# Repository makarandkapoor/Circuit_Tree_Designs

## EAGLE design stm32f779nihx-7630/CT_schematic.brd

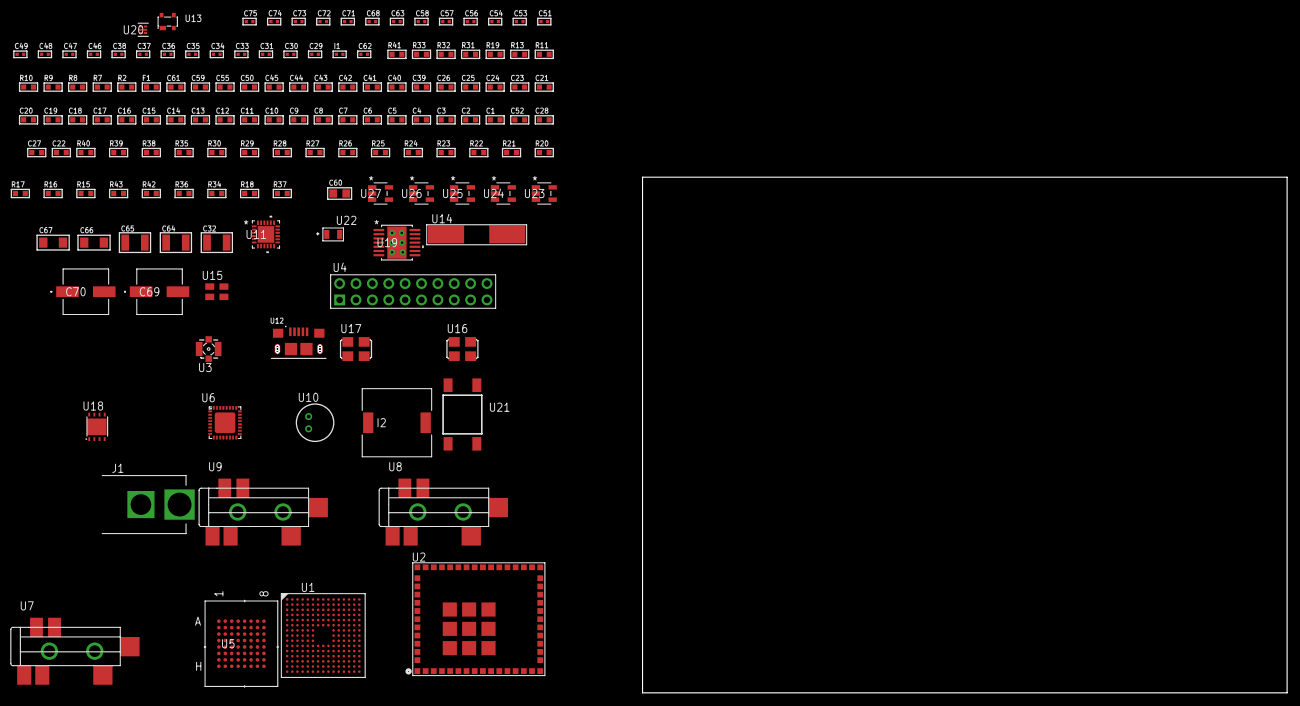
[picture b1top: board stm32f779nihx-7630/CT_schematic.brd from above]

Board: 2 copper layers, 142 parts (0 on the bottom side), 121 nets, no tracks yet.

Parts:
C1, C25, C39, C40, C41, C42, C43, C44, C45, C50, C55, C61: 1e-06; C0603
C2, C3, C4, C5, C6, C7, C8, C9, C10, C11, C12, C13, C14, C15, C16, C17, C18, C19, C20, C21, C23, C26: 1e-07; C0603
C22: 4.7e-06; C0603
C24: 1e-08; C0603
C27, C28, C52: 2.2e-06; C0603
C29, C30: 1e-11; C0402
C31: 1e-12; C0402
C32, C64, C65: 2.2e-05; C1210
C33, C34, C35, C36, C46, C47, C48, C49, C63, C68: 1e-07; C0402
C37, C38, C51, C53, C54, C56, C57, C58, C71, C72, C73, C74, C75: 1e-08; C0402
C59: 8e-07; R0603
C60: 1e-05; C0805
C62: 3.3e-09; C0402
C66, C67: 1e-05; C1206
C69, C70: 0.0001; EXV-9H
F1: 240.0; L0603
I1: 3.6e-09; C0402
I2: 5.2e-06; DR1040
J1: PJ-037B; PJ-037B_PACKAGE
R2: 1000.0; R0603
R7, R8, R9, R10: 4700.0; R0603
R11, R13: 2200.0; R0603
R15, R16, R17, R20, R21, R22, R23, R24, R25, R26, R27, R28, R29, R30, R39, R40: 10000.0; R0603
R18, R34, R36: 100000.0; R0603
R19: 2700.0; R0603
R31, R32: 1270.0; R0603
R33: 8060.0; R0603
R35: 36000.0; R0603
R37: 71007.101651032; R0603
R38: 22000.0; R0603
R41: 9100.0; R0603
R42: 680000.0; R0603
R43: 120000.0; R0603
U1: STM32F779NIH6; TFBGA216
U2: CC3200MODR1M2AMOBT; LGA63S127P16X13_2050X1750X150
U3: 73412-0114; COAXIAL_C
U4: TST-110-05-T-D-RA
U5: MT28EW128ABA1HPC-0SIT; LBGA-64
U6: SGTL5000XNAA3; QFN-32
U7, U8, U9: SJ-43515TS-SMT-TR
U10: WM-64PCT; WM-64PC
U11: USB3317C-CP-TR; QFN-24
U12: 10118193-0001LF; FCI_10118193-0001LF
U13: prtr5v0u2ax; SOT143B
U14: ABLS-25.000MHZ-B2F-T
U15: ASEK-32.768KHz-ECST; ASEK
U16: ASFL-24.57MHZ-NCS; ASFL1
U17: ASFL1-26MHZ-NCS; ASFL1
U18: LP2951ACSDX/NOPB; WSON-8
U19: tps54325PWP; HTSSOP14
U20: TPS3895ADRYR; SON-6
U21: 4-1437565-2; SW_4-1437565-2
U22: Q65110A2395; LGM67K-G1J2-24-Z
U23, U24, U25, U26, U27: nc7sz125m5x; NC7SZ125M5X

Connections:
CLK_CRYSTAL_U1_G1: C29.1, U1.G1, U14.1
CLK_CRYSTAL_U1_H1: C30.1, U1.H1, U14.2
CLK_U1_E1: U1.E1, U15.3
CLK_U6_21: U6.21, U16.3
CLK_U11_23: U11.23, U17.3
GND: C1.2, C2.2, C3.2, C4.2, C5.2, C6.2, C7.2, C8.2, C9.2, C10.2, C11.2, C12.2, C13.2, C14.2, C15.2, C16.2, C17.2, C18.2, C19.2, C20.2, C21.2, C22.2, C23.2, C24.2, C25.2, C26.2, C27.2, C28.2, C29.2, C30.2, C31.2, C32.2, C33.2, C34.2, C35.2, C36.2, C37.2, C38.2, C46.2, C47.2, C48.2, C49.2, C50.2, C51.2, C52.2, C53.2, C54.2, C55.2, C56.2, C57.2, C58.2, C59.2, C60.2, C61.2, C62.2, C64.2, C65.2, C66.2, C67.2, C68.2, C69.2, C70.2, C71.2, C72.2, C73.2, C74.2, C75.2, J1.2, R2.2, R15.2, R17.2, R18.2, R19.2, R25.2, R32.2, R33.2, R36.2, R38.2, R41.2, R43.2, U1.F2, U1.F6, U1.F7, U1.F8, U1.F9, U1.F10, U1.G6, U1.G10, U1.G12, U1.H6, U1.H10, U1.J6, U1.J10, U1.K6, U1.K7, U1.K8, U1.K9, U1.K10, U1.L6, U1.M1, U1.N1, U2.1, U2.2, U2.16, U2.27, U2.28, U2.30, U2.32, U2.38, U2.43, U2.55, U2.56, U2.57, U2.58, U2.59, U2.60, U2.61, U2.62, U2.63, U3.1, U3.2, U3.3, U3.4, U4.4, U4.6, U4.8, U4.10, U4.12, U4.14, U4.16, U4.18, U4.20, U5.E8, U5.H2, U5.H7, U6.1, U6.3, U6.7, U6.EXP, U8.1, U9.1, U10.2, U11.25, U12.5, U12.6, U12.7, U12.8, U12.9, U13.1, U15.2, U16.2, U17.2, U18.3, U18.4, U18.PAD, U19.5, U19.8, U19.9, U19.15, U20.2, U22.C, U23.2, U23.3, U24.1, U24.3, U25.1, U25.3, U26.1, U26.3, U27.1, U27.3
NET_U1_A7: R11.1, U1.A7, U2.3
NET_U1_B4: R13.1, U1.B4, U2.4
NET_U1_E5: R16.1, U1.E5
NET_U1_E6: R15.1, U1.E6
NET_U1_E11: C28.1, U1.E11
NET_U1_J1: R9.1, U1.J1, U26.4
NET_U1_L5: R17.1, U1.L5
NET_U1_L11: C27.1, U1.L11
NET_U1_R1: C24.1, C25.1, F1.1, U1.P1, U1.R1
NET_U1_R15: U21.3, U21.4
NET_U2_21: R18.1, U2.21
NET_U2_23: R19.1, U2.23
NET_U2_35: R8.1, U2.35, U25.4
NET_U3_1: C31.1, I1.1, U3.1
NET_U4_19: R25.1, U4.19
NET_U5_B4: R29.1, U5.B4
NET_U5_B5: R7.1, U5.B5, U24.4
NET_U6_10: C49.1, U6.10
NET_U6_29: R31.1, U6.29
NET_U6_31: R32.1, U6.31
NET_U7_1: U6.4, U7.1
NET_U7_2: U6.2, U7.2
NET_U7_5: U6.6, U7.5
NET_U8_2: C40.1, U8.2
NET_U8_5: C39.1, U8.5
NET_U9_2: C42.1, C43.1, U9.2
NET_U9_5: C41.1, U9.5
NET_U9_13: C42.2, C43.2
NET_U10_1: C44.1, C45.1, C50.1, U6.16, U10.1
NET_U10_15: C44.2, C45.2
NET_U11_4: C52.1, U11.4
NET_U11_22: R10.1, U11.22, U27.4
NET_U11_24: R33.1, U11.24
NET_U12_1: C55.1, U11.2, U12.1, U13.4
NET_U12_2: U11.5, U12.2, U13.3
NET_U12_3: U11.6, U12.3, U13.2
NET_U18_5: R34.1, U18.5
NET_U18_7: R35.2, R36.1, U18.7
NET_U19_2: R37.2, R38.1, U19.2
NET_U19_3: C61.1, U19.3
NET_U19_4: C62.1, U19.4
NET_U19_10: C63.1, I2.1, U19.10, U19.11
NET_U19_12: C63.2, U19.12
NET_U20_1: R40.1, R41.1, U20.1
NET_U20_3: R42.2, R43.1, U20.3
NET_U20_4: R39.1, U20.4, U23.4, U24.2, U25.2, U26.2, U27.2
NET_U21_1: R2.1, U21.1, U21.2
PROC_FMC_A0: U1.D2, U5.E2
PROC_FMC_A1: U1.E2, U5.D2
PROC_FMC_A2: U1.G2, U5.C2
PROC_FMC_A3: U1.H2, U5.A2
PROC_FMC_A4: U1.J2, U5.B2
PROC_FMC_A5: U1.K3, U5.D3
PROC_FMC_A6: U1.M6, U5.C3
PROC_FMC_A7: U1.N6, U5.A3
PROC_FMC_A8: U1.P6, U5.B6
PROC_FMC_A9: U1.M8, U5.A6
PROC_FMC_A10: U1.N7, U5.C6
PROC_FMC_A11: U1.M7, U5.D6
PROC_FMC_A12: U1.M13, U5.B7
PROC_FMC_A13: U1.M12, U5.A7
PROC_FMC_A14: U1.N12, U5.C7
PROC_FMC_A15: U1.N11, U5.D7
PROC_FMC_A16: U1.N10, U5.E7
PROC_FMC_A17: U1.M10, U5.B3
PROC_FMC_A18: U1.M11, U5.C4
PROC_FMC_A19: U1.A2, U5.D5
PROC_FMC_A20: U1.A1, U5.D4
PROC_FMC_A21: U1.B1, U5.C5
PROC_FMC_A22: U1.B2, U5.B8
PROC_FMC_D0: U1.L12, U5.E3
PROC_FMC_D1: U1.K13, U5.H3
PROC_FMC_D2: U1.B12, U5.E4
PROC_FMC_D3: U1.C12, U5.H4
PROC_FMC_D4: U1.R8, U5.H5
PROC_FMC_D5: U1.N9, U5.E5
PROC_FMC_D6: U1.P9, U5.H6
PROC_FMC_D7: U1.R9, U5.E6
PROC_FMC_D8: U1.P10, U5.F3
PROC_FMC_D9: U1.R10, U5.G3
PROC_FMC_D10: U1.R12, U5.F4
PROC_FMC_D11: U1.P11, U5.G4
PROC_FMC_D12: U1.R11, U5.F5
PROC_FMC_D13: U1.L15, U5.G6
PROC_FMC_D14: U1.L14, U5.F6
PROC_FMC_D15: U1.K15, U5.G7
PROC_FMC_NBL0: R30.1, U1.A6, U5.F7
PROC_FMC_NE2: R26.1, U1.D9, U5.F2
PROC_FMC_NOE: R27.1, U1.D11, U5.G2
PROC_FMC_NWAIT: U1.B11, U5.A4
PROC_FMC_NWE: R28.1, U1.C10, U5.A5
PROC_I2S1_CK: U1.B8, U6.24
PROC_I2S1_SD: U1.A11, U6.26
PROC_I2S1_WS: U1.C8, U6.23
PROC_SYS_JTCK_SWCLK: R23.1, U1.A14, U4.9
PROC_SYS_JTDI: R21.1, U1.A13, U4.5
PROC_SYS_JTDO_SWO: U1.A10, U4.13
PROC_SYS_JTMS_SWDIO: R22.1, U1.A15, U4.7
PROC_SYS_JTRST: R20.1, U1.A9, U4.3
PROC_USB_OTG_HS_ULPI_CK: U1.P4, U11.12
PROC_USB_OTG_HS_ULPI_D0: U1.R2, U11.16
PROC_USB_OTG_HS_ULPI_D1: U1.R5, U11.15
PROC_USB_OTG_HS_ULPI_D2: U1.R4, U11.14
PROC_USB_OTG_HS_ULPI_D3: U1.P12, U11.13
PROC_USB_OTG_HS_ULPI_D4: U1.R13, U11.11
PROC_USB_OTG_HS_ULPI_D5: U1.L13, U11.10
PROC_USB_OTG_HS_ULPI_D6: U1.K14, U11.9
PROC_USB_OTG_HS_ULPI_D7: U1.A8, U11.8
PROC_USB_OTG_HS_ULPI_DIR: U1.F3, U11.19
PROC_USB_OTG_HS_ULPI_NXT: U1.H4, U11.18
PROC_USB_OTG_HS_ULPI_STP: U1.M2, U11.20
RST_OUT_U4_SRESET_B: R24.1, U4.15, U23.1
VCC_S1_12V5: C59.1, C66.1, C67.1, C69.1, C70.1, J1.1, U18.8, U19.7, U19.13, U19.14
VCC_TIER1_1V8: C46.1, C47.1, C54.1, C60.1, C71.1, C72.1, C73.1, C74.1, C75.1, R34.2, R35.1, U6.5, U6.30, U11.21, U18.1, U23.5, U24.5, U25.5, U26.5, U27.5
VCC_TIER1_3V3: C1.1, C2.1, C3.1, C4.1, C5.1, C6.1, C7.1, C8.1, C9.1, C10.1, C11.1, C12.1, C13.1, C14.1, C15.1, C16.1, C17.1, C18.1, C19.1, C20.1, C21.1, C22.1, C23.1, C26.1, C32.1, C33.1, C34.1, C35.1, C36.1, C37.1, C38.1, C48.1, C51.1, C53.1, C56.1, C57.1, C58.1, C64.1, C65.1, C68.1, F1.2, I2.2, R7.2, R8.2, R9.2, R10.2, R11.2, R13.2, R16.2, R20.2, R21.2, R22.2, R23.2, R24.2, R26.2, R27.2, R28.2, R29.2, R30.2, R31.2, R37.1, R39.2, R40.2, R42.1, U1.C1, U1.E7, U1.E8, U1.E9, U1.E10, U1.F4, U1.F5, U1.F11, U1.G5, U1.G11, U1.H5, U1.H11, U1.J5, U1.J11, U1.K5, U1.K11, U1.L7, U1.L8, U1.L9, U1.L10, U2.36, U2.37, U2.40, U4.1, U4.2, U5.D8, U5.F1, U5.G5, U6.20, U11.3, U11.17, U15.4, U16.4, U17.4, U19.1, U20.6

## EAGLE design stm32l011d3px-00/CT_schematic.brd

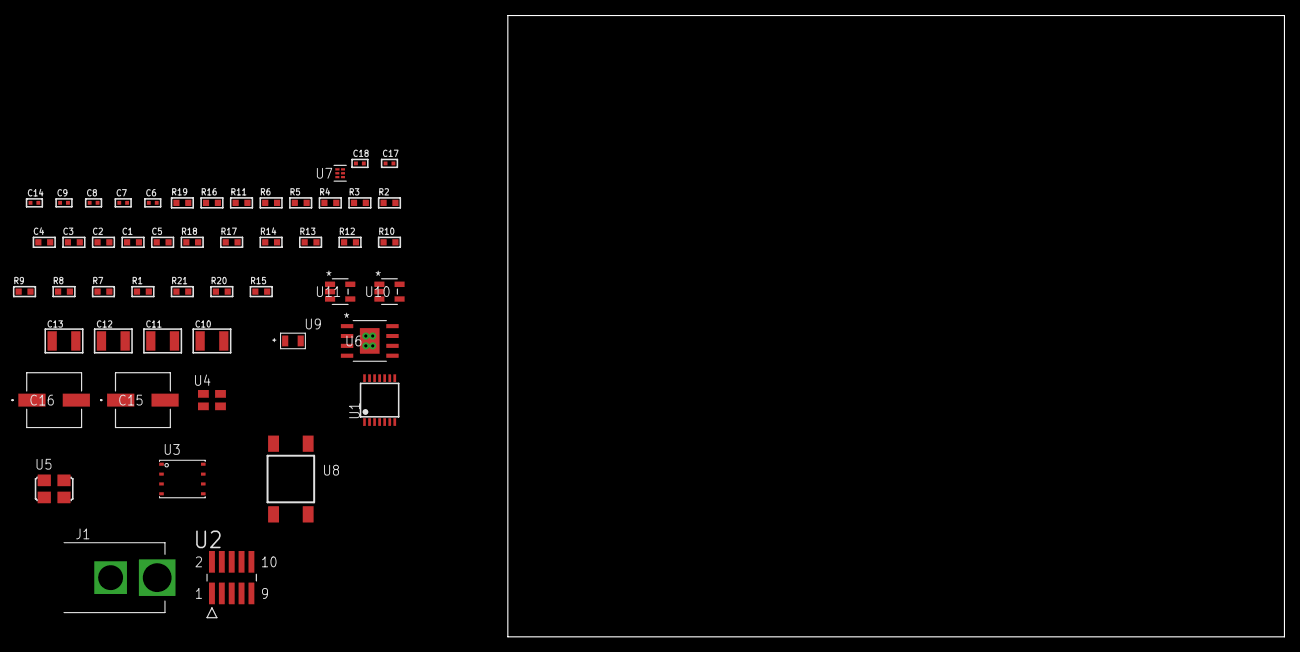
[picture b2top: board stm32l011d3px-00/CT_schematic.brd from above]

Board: 2 copper layers, 100.0 x 80.0 mm, 51 parts (0 on the bottom side), 23 nets, no tracks yet.

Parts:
C1, C2, C3, C4: 1e-07; C0603
C5: 4.7e-06; C0603
C6, C14: 1e-07; C0402
C7, C8, C9, C17, C18: 1e-08; C0402
C10, C11, C12, C13: 1e-05; C1210
C15, C16: 0.0001; EXV-9H
J1: PJ-037B; PJ-037B_PACKAGE
R1, R7, R8, R9, R10, R12, R13, R14, R17, R18: 10000.0; R0603
R2: 1000.0; R0603
R3: 1600.5; R0603
R4: 4700.0; R0603
R5, R6, R16: 2200.0; R0603
R11: 5.0; R0603
R15: 4031.5447154472; R0603
R19: 9100.0; R0603
R20: 680000.0; R0603
R21: 120000.0; R0603
U1: STM32L011D3P6; TSSOP14
U2: FTSH-105-01-L-DV-K; SAMTEC_FTSH-105-01-L-DV-K
U3: 24AA256-I/MF; DFN8-S
U4: ASEK-32.768KHz-ECST; ASEK
U5: ASFL1-12MHZ-NCS; ASFL1
U6: MIC5234YME; SOIC-8_EP
U7: TPS3895ADRYR; SON-6
U8: 4-1437565-2; SW_4-1437565-2
U9: Q65110A2395; LGM67K-G1J2-24-Z
U10, U11: nc7sz125m5x; NC7SZ125M5X

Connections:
CLK_U1_2: U1.2, U4.3
CLK_U1_5: U1.5, U5.3
GND: C1.2, C2.2, C3.2, C4.2, C5.2, C6.2, C7.2, C8.2, C9.2, C10.2, C11.2, C12.2, C13.2, C14.2, C15.2, C16.2, C17.2, C18.2, J1.2, R2.2, R7.2, R11.2, R16.2, R19.2, R21.2, U1.9, U2.3, U2.5, U3.4, U3.7, U4.2, U5.2, U6.7, U6.EPAD, U7.2, U9.C, U10.2, U10.3, U11.1, U11.3
NET_U1_1: R7.1, U1.1
NET_U1_4: R4.1, U1.4, U11.4
NET_U1_7: R5.1, U1.7, U3.6
NET_U1_8: R3.1, U1.8, U9.A
NET_U1_11: R1.1, U1.11, U8.3, U8.4
NET_U1_12: R6.1, U1.12, U3.5
NET_U2_9: R11.1, U2.9
NET_U3_1: R12.1, U3.1
NET_U3_2: R13.1, U3.2
NET_U3_3: R14.1, U3.3
NET_U6_4: R15.2, R16.1, U6.4
NET_U7_1: R18.1, R19.1, U7.1
NET_U7_3: R20.2, R21.1, U7.3
NET_U7_4: R17.1, U7.4, U10.4, U11.2
NET_U8_1: R2.1, U8.1, U8.2
PROC_SYS_SWCLK: R9.1, U1.14, U2.4
PROC_SYS_SWDIO: R10.1, U1.13, U2.2
RST_OUT_U2_JTAG_RST_B: R8.1, U2.10, U10.1
VCC_S1_16V8: C10.1, C11.1, C15.1, C16.1, J1.1, U6.5, U6.8
VCC_TIER1_3V3: C1.1, C2.1, C3.1, C4.1, C5.1, C6.1, C7.1, C8.1, C9.1, C12.1, C13.1, C14.1, C17.1, C18.1, R1.2, R3.2, R4.2, R5.2, R6.2, R8.2, R9.2, R10.2, R12.2, R13.2, R14.2, R15.1, R17.2, R18.2, R20.1, U1.10, U2.1, U3.8, U4.4, U5.4, U6.1, U7.6, U10.5, U11.5

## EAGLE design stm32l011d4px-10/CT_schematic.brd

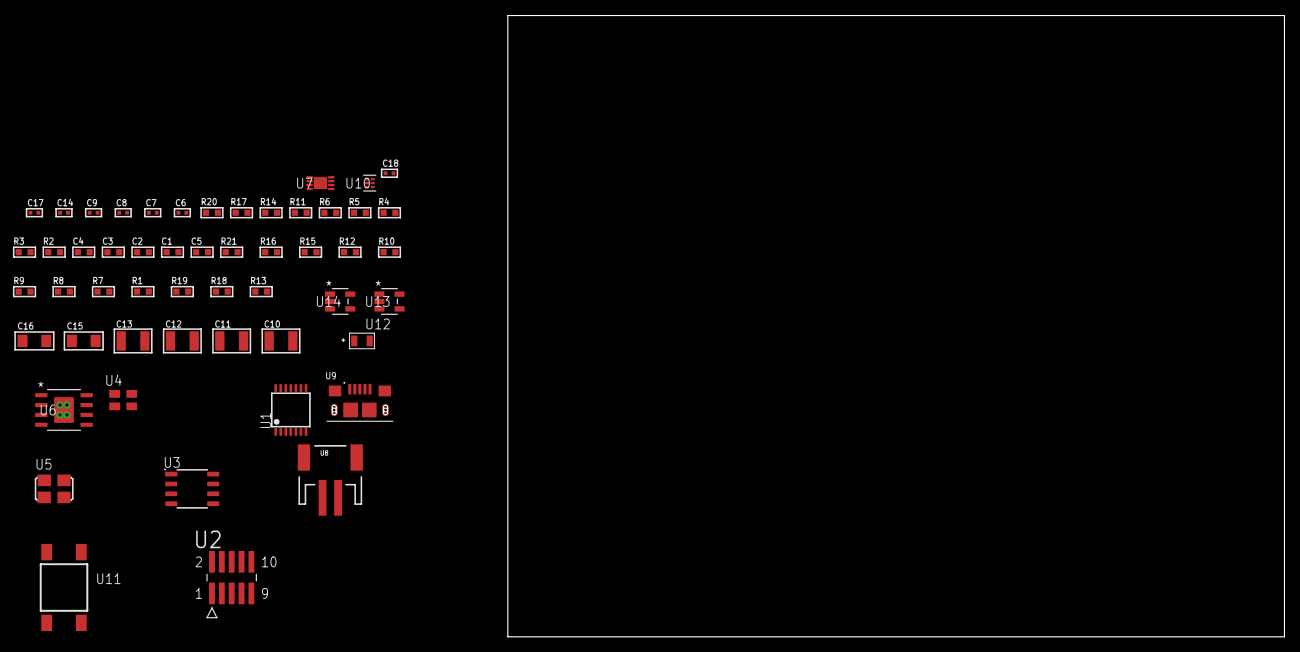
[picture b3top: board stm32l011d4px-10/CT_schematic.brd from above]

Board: 2 copper layers, 122.6 x 80.0 mm, 53 parts (0 on the bottom side), 24 nets, no tracks yet.

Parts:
C1, C2, C3, C4: 1e-07; C0603
C5: 4.7e-06; C0603
C6, C14: 1e-07; C0402
C7, C8, C9, C17, C18: 1e-08; C0402
C10, C11, C12, C13: 1e-05; C1210
C15, C16: 1e-05; C1206
R1, R7, R8, R9, R10, R12, R15, R16, R21: 10000.0; R0603
R2: 1000.0; R0603
R3: 1600.5; R0603
R4: 4700.0; R0603
R5, R6, R14: 2200.0; R0603
R11: 5.0; R0603
R13: 4031.5447154472; R0603
R17: 9100.0; R0603
R18: 680000.0; R0603
R19: 120000.0; R0603
R20: 2000.0; R0603
U1: STM32L011D4P7; TSSOP14
U2: FTSH-105-01-L-DV-K; SAMTEC_FTSH-105-01-L-DV-K
U3: M24M02-DRMN6TP; SOIC-8
U4: ASEK-32.768KHz-ECST; ASEK
U5: ASFL1-12MHZ-NCS; ASFL1
U6: MIC5234YME; SOIC-8_EP
U7: MCP73831T-2ACI/MC; DFN8_2X3MC
U8: S2B-PH-SM4-TB(LF)(SN); JST-2-SMD
U9: 10118193-0001LF; FCI_10118193-0001LF
U10: TPS3895ADRYR; SON-6
U11: 4-1437565-2; SW_4-1437565-2
U12: Q65110A2395; LGM67K-G1J2-24-Z
U13, U14: nc7sz125m5x; NC7SZ125M5X

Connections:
CLK_U1_2: U1.2, U4.3
CLK_U1_5: U1.5, U5.3
GND: C1.2, C2.2, C3.2, C4.2, C5.2, C6.2, C7.2, C8.2, C9.2, C10.2, C11.2, C12.2, C13.2, C14.2, C15.2, C16.2, C17.2, C18.2, R2.2, R7.2, R11.2, R12.2, R14.2, R17.2, R19.2, R20.2, U1.9, U2.3, U2.5, U3.4, U4.2, U5.2, U6.7, U6.EPAD, U7.6, U7.9, U8.2, U9.5, U9.6, U9.7, U9.8, U9.9, U10.2, U12.C, U13.2, U13.3, U14.1, U14.3
INPUT_USBPOWER_5V: C15.1, R21.2, U7.1, U7.2, U9.1
NET_U1_1: R7.1, U1.1
NET_U1_4: R4.1, U1.4, U14.4
NET_U1_7: R5.1, U1.7, U3.6
NET_U1_8: R3.1, U1.8, U12.A
NET_U1_11: R1.1, U1.11, U11.3, U11.4
NET_U1_12: R6.1, U1.12, U3.5
NET_U2_9: R11.1, U2.9
NET_U3_3: R12.1, U3.3
NET_U6_4: R13.2, R14.1, U6.4
NET_U7_5: R21.1, U7.5
NET_U7_8: R20.1, U7.8
NET_U10_1: R16.1, R17.1, U10.1
NET_U10_3: R18.2, R19.1, U10.3
NET_U10_4: R15.1, U10.4, U13.4, U14.2
NET_U11_1: R2.1, U11.1, U11.2
PROC_SYS_SWCLK: R9.1, U1.14, U2.4
PROC_SYS_SWDIO: R10.1, U1.13, U2.2
RST_OUT_U2_JTAG_RST_B: R8.1, U2.10, U13.1
VCC_S1_3V7: C10.1, C11.1, C16.1, U6.5, U6.8, U7.3, U7.4, U8.1
VCC_TIER1_3V3: C1.1, C2.1, C3.1, C4.1, C5.1, C6.1, C7.1, C8.1, C9.1, C12.1, C13.1, C14.1, C17.1, C18.1, R1.2, R3.2, R4.2, R5.2, R6.2, R8.2, R9.2, R10.2, R13.1, R15.2, R16.2, R18.1, U1.10, U2.1, U3.8, U4.4, U5.4, U6.1, U10.6, U13.5, U14.5

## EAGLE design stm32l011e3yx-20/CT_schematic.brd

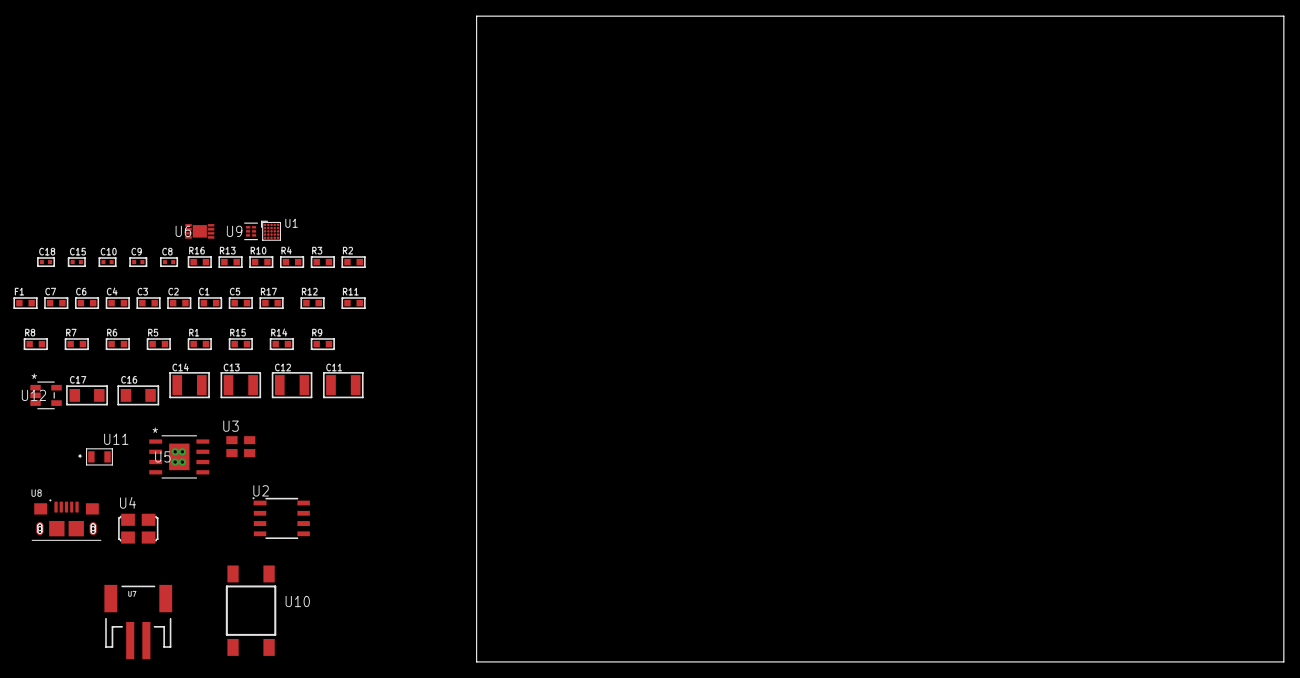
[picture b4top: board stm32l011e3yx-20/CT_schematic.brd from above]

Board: 2 copper layers, 154.3 x 80.0 mm, 48 parts (0 on the bottom side), 23 nets, no tracks yet.

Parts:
C1, C2, C3, C4: 1e-07; C0603
C5: 4.7e-06; C0603
C6: 1e-08; C0603
C7: 1e-06; C0603
C8, C9, C10, C18: 1e-08; C0402
C11, C12, C13, C14: 1e-05; C1210
C15: 1e-07; C0402
C16, C17: 1e-05; C1206
F1: 240.0; L0603
R1, R5, R6, R7, R8, R11, R12, R17: 10000.0; R0603
R2: 1000.0; R0603
R3: 1600.5; R0603
R4: 4700.0; R0603
R9: 4031.5447154472; R0603
R10: 2200.0; R0603
R13: 9100.0; R0603
R14: 680000.0; R0603
R15: 120000.0; R0603
R16: 2000.0; R0603
U1: STM32L011E3Y6; WLCSP25
U2: AT25020B-SSHL-T; SOIC-8
U3: ASEK-32.768KHz-ECST; ASEK
U4: ASFL1-12MHZ-NCS; ASFL1
U5: MIC5234YME; SOIC-8_EP
U6: MCP73831T-2ACI/MC; DFN8_2X3MC
U7: S2B-PH-SM4-TB(LF)(SN); JST-2-SMD
U8: 10118193-0001LF; FCI_10118193-0001LF
U9: TPS3895ADRYR; SON-6
U10: 4-1437565-2; SW_4-1437565-2
U11: Q65110A2395; LGM67K-G1J2-24-Z
U12: nc7sz125m5x; NC7SZ125M5X

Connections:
CLK_U1_B5: U1.B5, U3.3
GND: C1.2, C2.2, C3.2, C4.2, C5.2, C6.2, C7.2, C8.2, C9.2, C10.2, C11.2, C12.2, C13.2, C14.2, C15.2, C16.2, C17.2, C18.2, R2.2, R5.2, R10.2, R13.2, R15.2, R16.2, U1.E1, U2.4, U3.2, U4.2, U5.7, U5.EPAD, U6.6, U6.9, U7.2, U8.5, U8.6, U8.7, U8.8, U8.9, U9.2, U11.C, U12.1, U12.3
INPUT_USBPOWER_5V: C16.1, R17.2, U6.1, U6.2, U8.1
NET_U1_A5: R5.1, U1.A5
NET_U1_C4: C6.1, C7.1, F1.1, U1.C4
NET_U1_D5: R4.1, U1.D5, U12.4
NET_U1_E4: R3.1, U1.E4, U11.A
NET_U1_E5: R1.1, U1.E5, U4.3, U10.3, U10.4
NET_U2_3: R6.1, U2.3
NET_U2_7: R8.1, U2.7
NET_U5_4: R9.2, R10.1, U5.4
NET_U6_5: R17.1, U6.5
NET_U6_8: R16.1, U6.8
NET_U9_1: R12.1, R13.1, U9.1
NET_U9_3: R14.2, R15.1, U9.3
NET_U9_4: R11.1, U9.4, U12.2
NET_U10_1: R2.1, U10.1, U10.2
PROC_SPI1_MISO: U1.A2, U2.2
PROC_SPI1_MOSI: U1.C3, U2.5
PROC_SPI1_NSS: R7.1, U1.B3, U2.1
PROC_SPI1_SCK: U1.A1, U2.6
VCC_S1_3V7: C11.1, C12.1, C17.1, U5.5, U5.8, U6.3, U6.4, U7.1
VCC_TIER1_3V3: C1.1, C2.1, C3.1, C4.1, C5.1, C8.1, C9.1, C10.1, C13.1, C14.1, C15.1, C18.1, F1.2, R1.2, R3.2, R4.2, R6.2, R7.2, R8.2, R9.1, R11.2, R12.2, R14.1, U1.D1, U2.8, U3.4, U4.4, U5.1, U9.6, U12.5

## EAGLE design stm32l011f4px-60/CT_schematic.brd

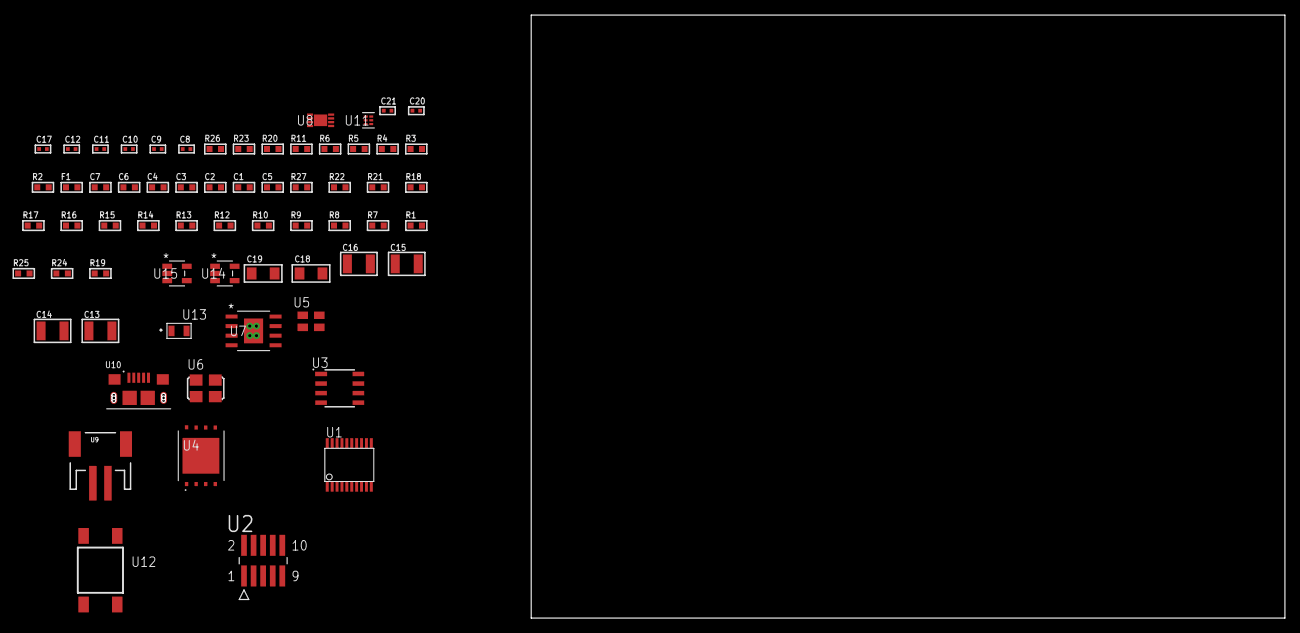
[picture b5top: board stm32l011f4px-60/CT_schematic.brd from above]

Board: 2 copper layers, 64 parts (0 on the bottom side), 34 nets, no tracks yet.

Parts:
C1, C2, C3, C4: 1e-07; C0603
C5: 4.7e-06; C0603
C6: 1e-08; C0603
C7: 1e-06; C0603
C8, C17: 1e-07; C0402
C9, C10, C11, C12, C20, C21: 1e-08; C0402
C13, C14, C15, C16: 1e-05; C1210
C18, C19: 1e-05; C1206
F1: 240.0; L0603
R1, R7, R8, R9, R10, R12, R13, R14, R15, R16, R17, R18, R21, R22, R27: 10000.0; R0603
R2: 1000.0; R0603
R3: 1600.5; R0603
R4: 4700.0; R0603
R5, R6, R20: 2200.0; R0603
R11: 5.0; R0603
R19: 4031.5447154472; R0603
R23: 9100.0; R0603
R24: 680000.0; R0603
R25: 120000.0; R0603
R26: 2000.0; R0603
U1: STM32L011F4P6; TSSOP20-I
U2: FTSH-105-01-L-DV-K; SAMTEC_FTSH-105-01-L-DV-K
U3: AT24C02D-SSHM-T; AT24C02D
U4: S25FL128SDPNFI001; WNG008
U5: ASEK-32.768KHz-ECST; ASEK
U6: ASFL1-12MHZ-NCS; ASFL1
U7: MIC5234YME; SOIC-8_EP
U8: MCP73831T-2ACI/MC; DFN8_2X3MC
U9: S2B-PH-SM4-TB(LF)(SN); JST-2-SMD
U10: 10118193-0001LF; FCI_10118193-0001LF
U11: TPS3895ADRYR; SON-6
U12: 4-1437565-2; SW_4-1437565-2
U13: Q65110A2395; LGM67K-G1J2-24-Z
U14, U15: nc7sz125m5x; NC7SZ125M5X

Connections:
CLK_U1_2: U1.2, U5.3
CLK_U1_6: U1.6, U6.3
GND: C1.2, C2.2, C3.2, C4.2, C5.2, C6.2, C7.2, C8.2, C9.2, C10.2, C11.2, C12.2, C13.2, C14.2, C15.2, C16.2, C17.2, C18.2, C19.2, C20.2, C21.2, R2.2, R7.2, R11.2, R12.2, R14.2, R15.2, R20.2, R23.2, R25.2, R26.2, U1.15, U2.3, U2.5, U3.4, U4.4, U4.PAD, U5.2, U6.2, U7.7, U7.EPAD, U8.6, U8.9, U9.2, U10.5, U10.6, U10.7, U10.8, U10.9, U11.2, U13.C, U14.2, U14.3, U15.1, U15.3
INPUT_USBPOWER_5V: C18.1, R27.2, U8.1, U8.2, U10.1
NET_U1_1: R7.1, U1.1
NET_U1_4: R4.1, U1.4, U15.4
NET_U1_5: C6.1, C7.1, F1.1, U1.5
NET_U1_9: R3.1, U1.9, U13.A
NET_U1_14: R1.1, U1.14, U12.3, U12.4
NET_U1_17: R5.1, U1.17, U3.6
NET_U1_18: R6.1, U1.18, U3.5
NET_U2_9: R11.1, U2.9
NET_U3_1: R13.1, U3.1
NET_U3_2: R14.1, U3.2
NET_U3_3: R15.1, U3.3
NET_U3_7: R12.1, U3.7
NET_U4_3: R16.1, U4.3
NET_U4_7: R18.1, U4.7
NET_U7_4: R19.2, R20.1, U7.4
NET_U8_5: R27.1, U8.5
NET_U8_8: R26.1, U8.8
NET_U11_1: R22.1, R23.1, U11.1
NET_U11_3: R24.2, R25.1, U11.3
NET_U11_4: R21.1, U11.4, U14.4, U15.2
NET_U12_1: R2.1, U12.1, U12.2
PROC_SPI1_MISO: U1.12, U4.2
PROC_SPI1_MOSI: U1.13, U4.5
PROC_SPI1_NSS: R17.1, U1.10, U4.1
PROC_SPI1_SCK: U1.11, U4.6
PROC_SYS_SWCLK: R9.1, U1.20, U2.4
PROC_SYS_SWDIO: R10.1, U1.19, U2.2
RST_OUT_U2_JTAG_RST_B: R8.1, U2.10, U14.1
VCC_S1_3V7: C13.1, C14.1, C19.1, U7.5, U7.8, U8.3, U8.4, U9.1
VCC_TIER1_3V3: C1.1, C2.1, C3.1, C4.1, C5.1, C8.1, C9.1, C10.1, C11.1, C12.1, C15.1, C16.1, C17.1, C20.1, C21.1, F1.2, R1.2, R3.2, R4.2, R5.2, R6.2, R8.2, R9.2, R10.2, R13.2, R16.2, R17.2, R18.2, R19.1, R21.2, R22.2, R24.1, U1.16, U2.1, U3.8, U4.8, U5.4, U6.4, U7.1, U11.6, U14.5, U15.5

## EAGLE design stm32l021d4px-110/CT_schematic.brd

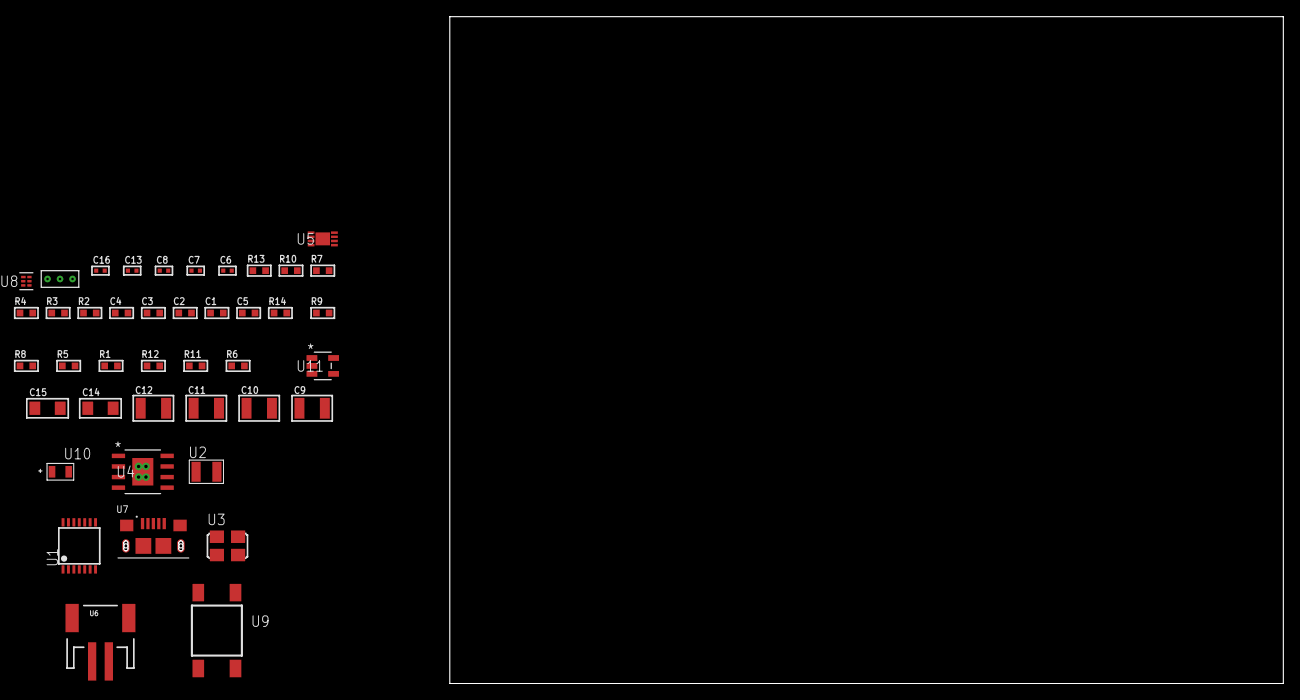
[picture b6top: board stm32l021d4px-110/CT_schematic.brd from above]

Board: 2 copper layers, 42 parts (0 on the bottom side), 20 nets, no tracks yet.

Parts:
C1, C2, C3, C4: 1e-07; C0603
C5: 4.7e-06; C0603
C6, C7: 1e-11; C0402
C8, C16: 1e-08; C0402
C9, C10, C11, C12: 1e-05; C1210
C13: 1e-07; C0402
C14, C15: 1e-05; C1206
R1, R5, R8, R9, R14: 10000.0; R0603
R2: 1000.0; R0603
R3: 1600.5; R0603
R4: 4700.0; R0603
R6: 4031.5447154472; R0603
R7: 2200.0; R0603
R10: 9100.0; R0603
R11: 680000.0; R0603
R12: 120000.0; R0603
R13: 2000.0; R0603
U1: STM32L021D4P6; TSSOP14
U2: ABS07-32.768KHZ-7-T
U3: ASFL1-12MHZ-NCS; ASFL1
U4: MIC5234YME; SOIC-8_EP
U5: MCP73831T-2ACI/MC; DFN8_2X3MC
U6: S2B-PH-SM4-TB(LF)(SN); JST-2-SMD
U7: 10118193-0001LF; FCI_10118193-0001LF
U8: TPS3895ADRYR; SON-6
U9: 4-1437565-2; SW_4-1437565-2
U10: Q65110A2395; LGM67K-G1J2-24-Z
U11: nc7sz125m5x; NC7SZ125M5X
U12: Dummy; DUMMY_PACKAGE_85

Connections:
CLK_CRYSTAL_U1_2: C6.1, U1.2, U2.1
CLK_CRYSTAL_U1_3: C7.1, U1.3, U2.2
CLK_U1_5: U1.5, U3.3
GND: C1.2, C2.2, C3.2, C4.2, C5.2, C6.2, C7.2, C8.2, C9.2, C10.2, C11.2, C12.2, C13.2, C14.2, C15.2, C16.2, R2.2, R5.2, R7.2, R10.2, R12.2, R13.2, U1.9, U3.2, U4.7, U4.EPAD, U5.6, U5.9, U6.2, U7.5, U7.6, U7.7, U7.8, U7.9, U8.2, U10.C, U11.1, U11.3, U12.1
INPUT_USBPOWER_5V: C14.1, R14.2, U5.1, U5.2, U7.1
NET_U1_1: R5.1, U1.1
NET_U1_4: R4.1, U1.4, U11.4
NET_U1_13: R3.1, U1.13, U10.A
NET_U1_14: R1.1, U1.14, U9.3, U9.4
NET_U4_4: R6.2, R7.1, U4.4
NET_U5_5: R14.1, U5.5
NET_U5_8: R13.1, U5.8
NET_U8_1: R9.1, R10.1, U8.1
NET_U8_3: R11.2, R12.1, U8.3
NET_U8_4: R8.1, U8.4, U11.2
NET_U9_1: R2.1, U9.1, U9.2
PROC_TIM2_CH2: U1.6, U12.3
PROC_TIM2_CH3: U1.12, U12.2
VCC_S1_3V7: C9.1, C10.1, C15.1, U4.5, U4.8, U5.3, U5.4, U6.1
VCC_TIER1_3V3: C1.1, C2.1, C3.1, C4.1, C5.1, C8.1, C11.1, C12.1, C13.1, C16.1, R1.2, R3.2, R4.2, R6.1, R8.2, R9.2, R11.1, U1.10, U3.4, U4.1, U8.6, U11.5

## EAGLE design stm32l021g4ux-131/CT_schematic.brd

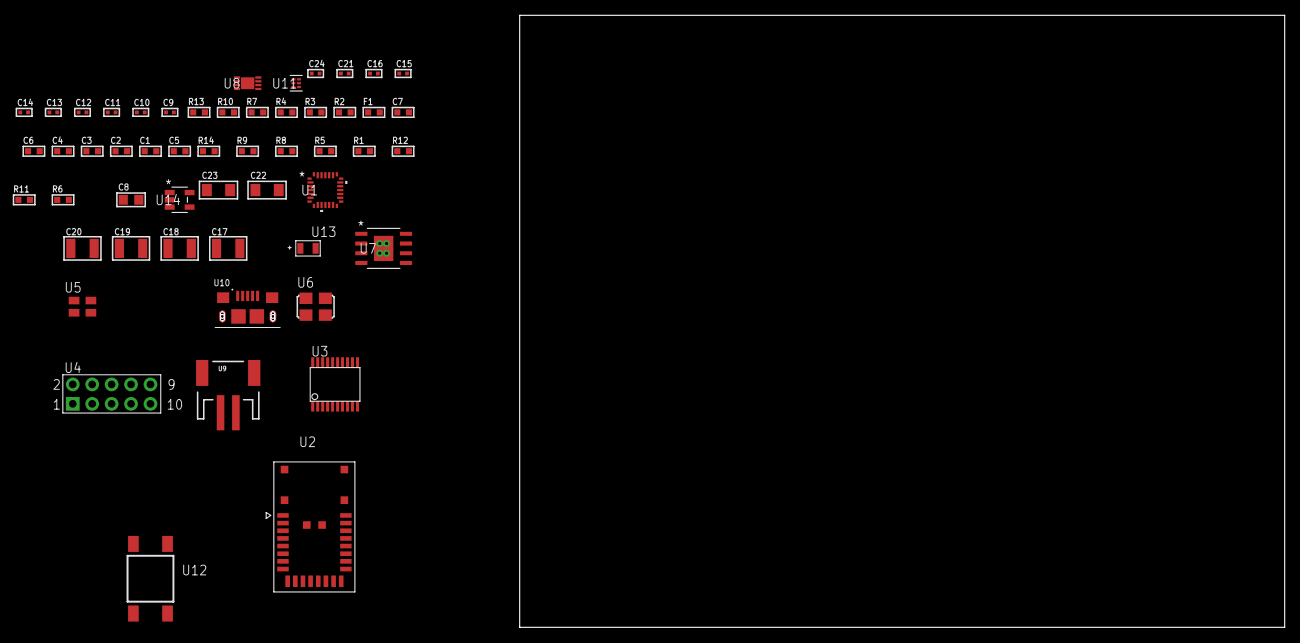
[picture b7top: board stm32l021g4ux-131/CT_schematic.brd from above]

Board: 2 copper layers, 53 parts (0 on the bottom side), 36 nets, no tracks yet.

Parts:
C1, C2, C3, C4: 1e-07; C0603
C5: 4.7e-06; C0603
C6: 1e-08; C0603
C7: 1e-06; C0603
C8: 1e-05; C0805
C9, C10, C11, C12, C13, C14, C21: 1e-07; C0402
C15, C16, C24: 1e-08; C0402
C17, C18, C19, C20: 1e-05; C1210
C22, C23: 1e-05; C1206
F1: 240.0; L0603
R1, R5, R8, R9, R14: 10000.0; R0603
R2: 1000.0; R0603
R3: 1600.5; R0603
R4: 4700.0; R0603
R6: 4031.5447154472; R0603
R7: 2200.0; R0603
R10: 9100.0; R0603
R11: 680000.0; R0603
R12: 120000.0; R0603
R13: 2000.0; R0603
U1: STM32L021G4U6; UFQFPN28
U2: A2500R24A00GM
U3: SP3203ECY-L/TR; TSSOP20-I
U4: HTSS-105-01-G-D
U5: ASEK-32.768KHz-ECST; ASEK
U6: ASFL1-12MHZ-NCS; ASFL1
U7: MIC5234YME; SOIC-8_EP
U8: MCP73831T-2ACI/MC; DFN8_2X3MC
U9: S2B-PH-SM4-TB(LF)(SN); JST-2-SMD
U10: 10118193-0001LF; FCI_10118193-0001LF
U11: TPS3895ADRYR; SON-6
U12: 4-1437565-2; SW_4-1437565-2
U13: Q65110A2395; LGM67K-G1J2-24-Z
U14: nc7sz125m5x; NC7SZ125M5X

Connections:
CLK_U1_2: U1.2, U5.3
CLK_U1_6: U1.6, U6.3
GND: C1.2, C2.2, C3.2, C4.2, C5.2, C6.2, C7.2, C8.2, C9.2, C10.2, C13.2, C14.2, C15.2, C16.2, C17.2, C18.2, C19.2, C20.2, C21.2, C22.2, C23.2, C24.2, R2.2, R5.2, R7.2, R10.2, R12.2, R13.2, U1.16, U2.8, U2.17, U3.18, U4.9, U5.2, U6.2, U7.7, U7.EPAD, U8.6, U8.9, U9.2, U10.5, U10.6, U10.7, U10.8, U10.9, U11.2, U13.C, U14.1, U14.3
INPUT_USBPOWER_5V: C22.1, R14.2, U8.1, U8.2, U10.1
NET_U1_1: R5.1, U1.1
NET_U1_4: R4.1, U1.4, U14.4
NET_U1_5: C6.1, C7.1, F1.1, U1.5
NET_U1_27: R3.1, U1.27, U13.A
NET_U1_28: R1.1, U1.28, U12.3, U12.4
NET_U3_1: C11.1, U3.1
NET_U3_2: C13.1, U3.2
NET_U3_3: C11.2, U3.3
NET_U3_4: C12.1, U3.4
NET_U3_5: C12.2, U3.5
NET_U3_6: C14.1, U3.6
NET_U4_3: U3.14, U4.3
NET_U4_4: U3.13, U4.4
NET_U4_5: U3.17, U4.5
NET_U4_6: U3.16, U4.6
NET_U7_4: R6.2, R7.1, U7.4
NET_U8_5: R14.1, U8.5
NET_U8_8: R13.1, U8.8
NET_U11_1: R9.1, R10.1, U11.1
NET_U11_3: R11.2, R12.1, U11.3
NET_U11_4: R8.1, U11.4, U14.2
NET_U12_1: R2.1, U12.1, U12.2
PROC_LPUART1_CTS: U1.12, U3.8
PROC_LPUART1_RTS: U1.15, U3.10
PROC_LPUART1_RX: U1.9, U3.11
PROC_LPUART1_TX: U1.7, U3.7
PROC_SPI1_MISO: U1.14, U2.10
PROC_SPI1_MOSI: U1.13, U2.11
PROC_SPI1_NSS: U1.10, U2.12
PROC_SPI1_SCK: U1.11, U2.9
VCC_S1_3V7: C17.1, C18.1, C23.1, U7.5, U7.8, U8.3, U8.4, U9.1
VCC_TIER1_3V3: C1.1, C2.1, C3.1, C4.1, C5.1, C8.1, C9.1, C10.1, C15.1, C16.1, C19.1, C20.1, C21.1, C24.1, F1.2, R1.2, R3.2, R4.2, R6.1, R8.2, R9.2, R11.1, U1.17, U2.18, U3.12, U3.19, U5.4, U6.4, U7.1, U11.6, U14.5
